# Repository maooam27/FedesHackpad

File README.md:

# FedesHackpad

The FedesHackpad is my first real electric project, designed by me with the help of Hack Club during the Highway to Undercity event. It has 6 buttons customizable with several macros through its firmware in KMK and 2 LEDs. It will probably be improved, especially its firmware.

## Features
- Nice case made out of pure programmer tears
- 2 rgb LEDs SK6812
- 6 programmable keys

## CAD Model:
The model was made using Fusion360, it was my first time using this tool too and it is made by two main pieces, the top and the bottom one.
The top piece leaves space to cool down and see both the microcontroller and the LEDs.... it is not poor design :(

See! lovely <3

## PCB
The PCB was made in KiCad. I needed to import the OPL library.

Schematic:

PCB:

## Firmware
For the firmware I used KMK in python, however it's not perfect, I have to improve it, it's the first time I write one.
The desired functioning is:
- random rgb lights every now and then
- macros when pressing keys
- random rgb lights also when pressing keys

## BOM:
List with everything you would need to rebuild this hackpad:
- 1x XIAO RP2040
- 4x Cherry MX Switches
- 4x Cherry MX Keycaps
- 2x SK6812 mini RGB LEDs
- 1x 3D printed case (top and bottom parts)
- 4x nuts and bolts to keep the case closed

## Extra stuff
Well I might just say thank you Hack Club, I'm now 18 and during the last 2 years, I really loved coding and practicing my skills with all of the community around the world. Big thanks and love from Italy <3

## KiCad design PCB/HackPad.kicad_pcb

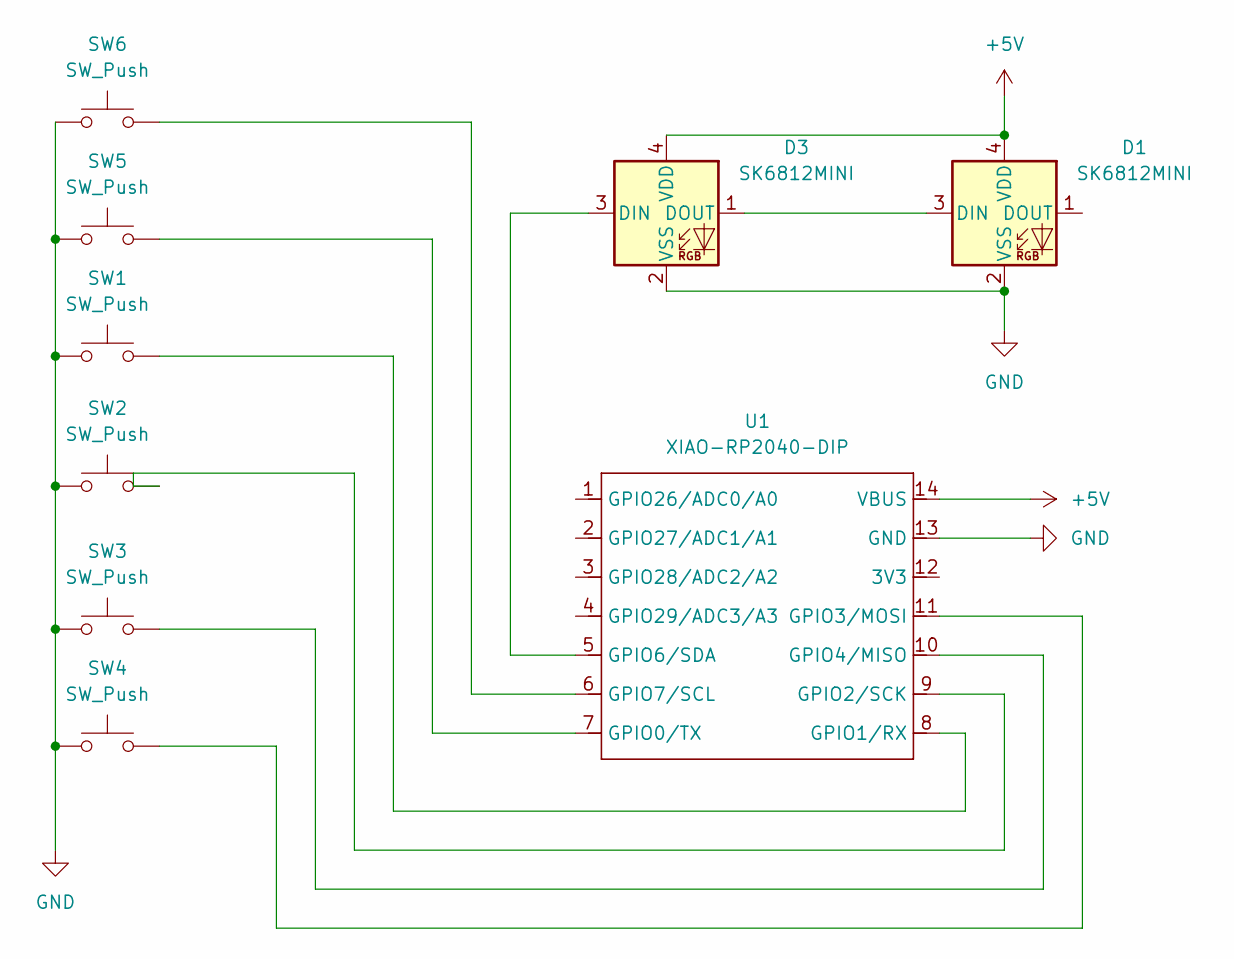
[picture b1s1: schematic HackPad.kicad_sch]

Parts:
D1, D3: SK6812MINI; LED_SK6812MINI_PLCC4_3.5x3.5mm_P1.75mm
SW1, SW2, SW3, SW4, SW5, SW6: SW_Push; SW_Cherry_MX_1.00u_PCB
U1: XIAO-RP2040-DIP

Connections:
+5V: D1.4 (VDD), D3.4 (VDD), U1.14 (VBUS)
GND: D1.2 (VSS), D3.2 (VSS), SW1.1, SW2.1, SW3.1, SW4.1, SW5.1, SW6.1, U1.13 (GND)
unnamed: D1.3 (DIN), D3.1 (DOUT)
unnamed: D3.3 (DIN), U1.5 (GPIO6/SDA)
unnamed: SW5.2, U1.7 (GPIO0/TX)
unnamed: SW1.2, U1.8 (GPIO1/RX)
unnamed: SW2.2, U1.9 (GPIO2/SCK)
unnamed: SW4.2, U1.11 (GPIO3/MOSI)
unnamed: SW3.2, U1.10 (GPIO4/MISO)
unnamed: SW6.2, U1.6 (GPIO7/SCL)

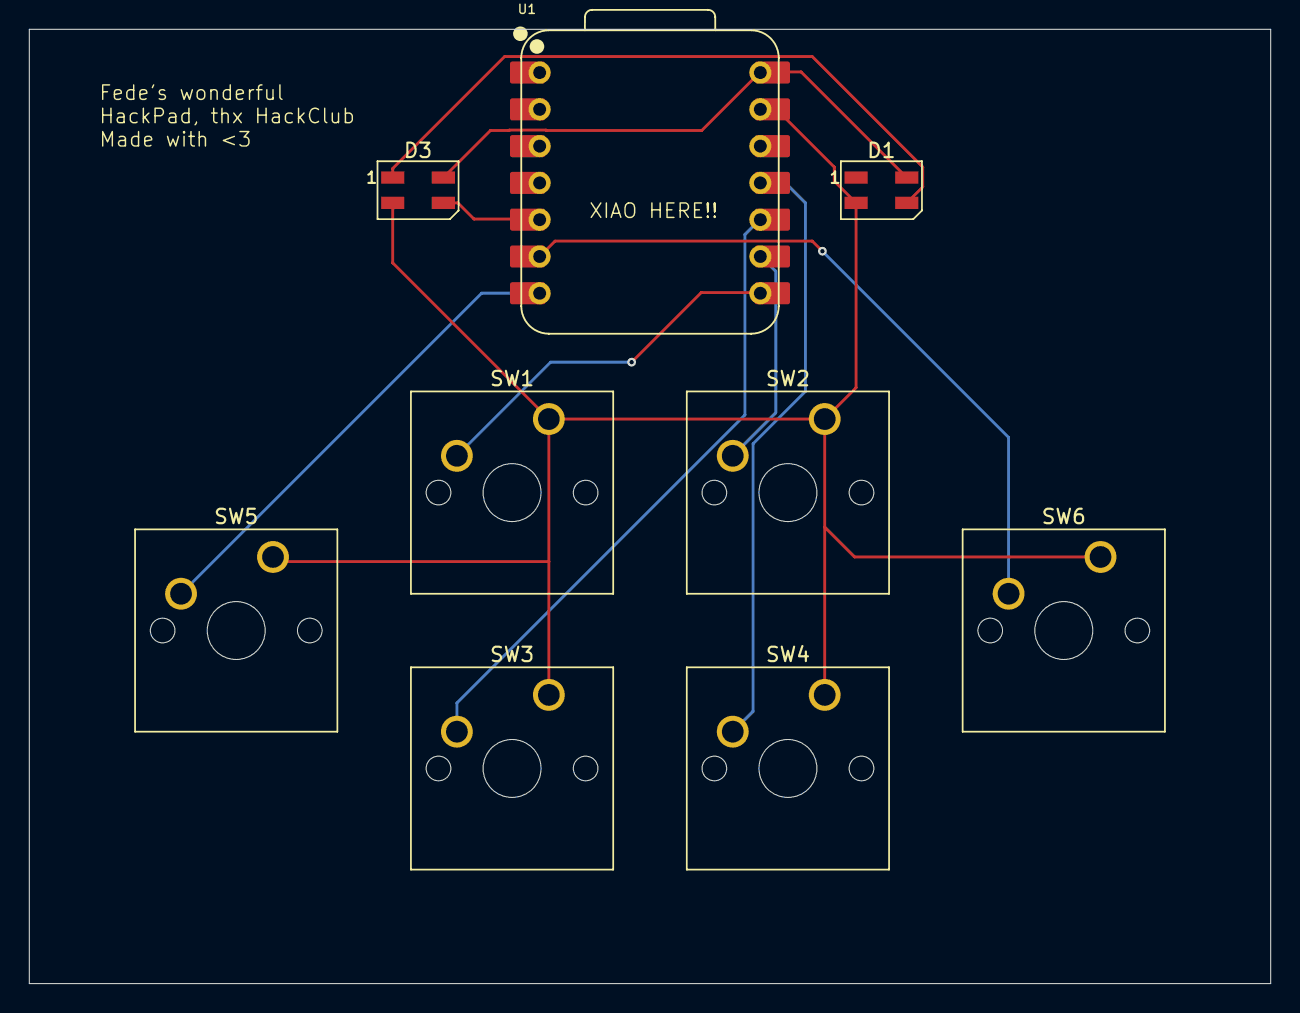
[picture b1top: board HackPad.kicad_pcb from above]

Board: 2 copper layers, 85.7 x 65.9 mm, 9 parts (0 on the bottom side), 10 nets.

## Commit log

2025-06-09 init
2025-06-09 corrected folders hierarchy
